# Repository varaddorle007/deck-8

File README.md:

# Deck-8

**An open-source 8-key macro pad with two knobs, a tiny screen and Bluetooth.** Everything is in this repo: the circuit board, the 3D-printable case, the firmware, and every file you need to order the parts.

*Click the preview for the full 30 second video with sound.*

> **Status: Rev A, designed and checked, but not yet built.** The board passes every automatic check (design rules, schematic checks, a fit check of the board in the case). The firmware compiles. But **no one has built one yet**, and the firmware has never run on real hardware. If you build one, you are the first. Please open an issue and tell us what happened, good or bad. See [Known risks](#known-risks).

## What it does

| | |
|---|---|
| **Keys** | 8 mechanical keys (MX-style, hot-swap, so you can change switches without soldering) in 2 rows of 4 |
| **Knobs** | 2 rotary knobs with push buttons (volume, scrolling, anything you map) |
| **Screen** | 0.96 inch OLED showing battery, connection and active layer |
| **Side buttons** | L1 and L2 on the left, System on the right, plus a power slide switch |
| **Lights** | RGB under every key, plus a glowing ring around the base |
| **Connections** | USB-C and Bluetooth (5 profiles) |
| **Battery** | Built-in 1000 mAh LiPo, charges over USB-C |
| **Brain** | Nordic nRF52840 (Raytac MDBT50Q module), running [ZMK](https://zmk.dev) firmware |
| **Remapping** | Change keys live in [ZMK Studio](https://zmk.studio), no rebuild needed |
| **Size** | Case 98 × 84 mm, 18 mm tall at the front rising to 30 mm at the back (the top tilts 8°). Board 92.8 × 76 mm, 4 layers |

### The layers

By default the 8 keys send **F13–F20**. No normal keyboard has those keys, so they never clash with anything. Bind them to anything you like in OBS, in your operating system, or in a Stream Deck-style app.

```
         [knob A]   [  OLED  ]   [knob B]
  [L1]   [ 1 ] [ 2 ] [ 3 ] [ 4 ]
  [L2]   [ 5 ] [ 6 ] [ 7 ] [ 8 ]            [SYS]
```

| Layer | How you get it | Keys 1–4 | Keys 5–8 | Knob A turn / press | Knob B turn / press |
|---|---|---|---|---|---|
| Bank 1 | default | F13 F14 F15 F16 | F17 F18 F19 F20 | volume / mute | ← → / play-pause |
| Media | hold L1 | prev, play/pause, next, mute | undo, redo, copy, paste | same | same |
| Bank 3 | hold L2 | Ctrl+F13–F16 | Ctrl+F17–F20 | same | same |
| System | hold SYS | Bluetooth profile 1–4 | clear profile, USB/Bluetooth, lights on/off, next effect | brightness / saturation | colour / unlock Studio |

On the System layer, L1 jumps to the bootloader (for updates) and L2 resets. Edit [`firmware/config/deck8.keymap`](firmware/config/deck8.keymap) to change any of this.

## Pictures

### The case

| | |
|---|---|
|  |  |
|  |  |
|  |  |

*Bottom right: the tray, with the battery on the left and the glowing ring's wall around the edge. The 3D renders show the board and its parts as simple boxes where a part has no 3D model.*

### How it stacks together

The board is a two-sided sandwich:

- **Underneath** are all the small electronic parts: the main chip, the charger, the USB-C port, the key lights and the 8 key sockets. The factory solders these on.
- **On top** are only the parts you touch: the 2 knobs and the screen.
- **The key switches are not soldered.** They push down from the top through a thin plate and click into the sockets underneath. A broken key is pulled out and replaced.

### The circuit board

| Top | Bottom |
|---|---|
|  |  |

| 3D view, top | 3D view, bottom |
|---|---|
|  |  |

The PCB 3D views show the bare board; most parts have no 3D model in KiCad's library.

Four layers: top (signals), a full ground plane, a split power plane (3.3 V and the LED supply), and the bottom (parts and signals). 1037 tracks, 585 vias, USB data lines 14.5 and 15.2 mm long with no vias.

| Ground layer | Power layer |
|---|---|
|  |  |

### The schematic

Seven sheets, all generated from [`hardware/tools/gen_schematic.py`](hardware/tools/gen_schematic.py). The full set is in [`docs/deck8-schematic.pdf`](docs/deck8-schematic.pdf).

| Power: USB-C, charger, regulator, LED switch | MCU: nRF52840 and crystal |
|---|---|
|  |  |

| Inputs: keys, buttons, knobs | Lighting | Display |
|---|---|---|
|  |  |  |

## Build one

This is the plain version. [`release/BUILD-GUIDE.md`](release/BUILD-GUIDE.md) has the same steps in more detail, and [`release/BUY-LIST.csv`](release/BUY-LIST.csv) lists every part.

### What it costs

An honest estimate, from October 2026 prices. **Check every number at the time you order:**

| Item | Rough cost |
|---|---|
| Assembled boards from JLCPCB (3–5 boards, with all the small parts, setup fees and shipping) | about $150–200 total (₹13,000–17,000) |
| Parts you buy yourself: screen, 2 encoders, battery, LED strip, 8 switches, keycaps, screws | about $20–35 per unit |
| Printing the case | about $10–35, depending on where you print |

The big cost is not the board itself. A bare board is cheap (5 boards for about $8 with leaded HASL finish). The cost is assembly: setup fees, "extended part" fees, the parts, and shipping. If you can solder, you can order bare boards and build them, but the main chip's pads are underneath it (see the next section), so you will need a hot-air station.

### Step 1: order the board

The ready-to-upload files are in [`release/deck8-RevA-manufacturing/1-PCB-order-JLCPCB/`](release/deck8-RevA-manufacturing/1-PCB-order-JLCPCB/):

| File | Upload it as |
|---|---|
| `deck8-RevA-gerbers.zip` | The board design |
| `deck8-RevA-bom-jlc.csv` | The parts list |
| `deck8-RevA-cpl-jlc.csv` | Where each part goes |

Settings (all listed in `JLC-ORDER-SETTINGS.md` in the same folder): 4 layers, 1.6 mm thick, ENIG finish (HASL also works but is less flat), tented vias, assembly on the **bottom side only**, and "Confirm parts placement" turned on.

**Watch for these on the JLCPCB parts page:**

- **The nRF52840 module (U5, MDBT50Q-1MV2) was out of stock** on 24 Oct 2026. Pick "Global Sourcing" for it, or buy it from Mouser or DigiKey and send it to JLC. Don't remove it from the order: its pads are under the module, so it can't be soldered by hand without hot air.
- **Four parts were swapped** to alternatives JLC had in stock. Each has the same footprint, checked against its datasheet: the 8 key sockets (HanElectricity CPG151101S11-16), the charger (BQ24074RGTT), the reset button (PTS810SJK) and the ring connector (Joint Tech A1001WR-S-03P).
- **Check the placement preview.** JLC doesn't know some of these parts' rotation. Check D1–D8, K1–K8, J4, SW1–SW5 and U5 sit correctly on their pads, and rotate any that don't.

### Step 2: buy the rest

[`release/BUY-LIST.csv`](release/BUY-LIST.csv) is the full list. Briefly:

- 2 × Bourns PEC11R-4220F-S0024 rotary encoders (through-hole)
- 4 × Würth 9774030243 M2 standoffs (SMD, not at LCSC)
- 0.96 inch SSD1306 I²C OLED module with its 4-pin header (pin order GND-VCC-SCL-SDA)
- 8 × MX-style switches and 8 × keycaps
- 1000 mAh LiPo with protection board and a JST-PH plug (**check the polarity**, see below)
- SK6812 LED strip (5 mm wide, 60 LEDs/m, 293 mm = 17 LEDs) and a 3-pin JST SH lead
- M2 hardware: 4 heat-set inserts (3 mm long), 4 × M2×5 **wafer-head** screws, 2 × M2×6 and 2 × M2×12 pan-head screws
- 4 rubber feet (8 mm), and a 1 mm acrylic lens (laser-cut from the DXF)
- To flash the bootloader once: a Tag-Connect TC2030-IDC-NL cable and an SWD probe

### Step 3: print the case

Files are in [`release/deck8-RevA-manufacturing/3-Enclosure/`](release/deck8-RevA-manufacturing/3-Enclosure/). All STLs are in millimetres, laid flat.

| Part | Qty | Material |
|---|---|---|
| Top shell | 1 | MJF or SLS nylon (best), or FDM PETG/ASA. Nylon takes heat-set inserts. |
| Bottom tray | 1 | MJF nylon or FDM PETG |
| Light ring | 1 | Clear or translucent (clear SLA resin, sanded frosted). It must let light through. |
| Knob | 2 | MJF nylon or SLA (one file, print two) |
| Buttons (L1, L2, System) | 1 each | MJF nylon or SLA |
| Switch plate | 1 | Laser-cut 1.5 mm steel, aluminium or FR-4 from the DXF (best), or printed |
| OLED lens | 1 | 1 mm clear or smoked acrylic, laser-cut from the DXF |

### Step 4: assemble

1. **Solder by hand:** the 4 standoffs on the bottom (ST1–ST4) and the 2 encoders on the top.
2. **Check power.** Plug in USB-C through a USB power meter: it should draw well under 100 mA. With the power switch on, TP2 (VSYS) should read about 4.4 V and TP4 (+3V3) 3.3 V, measured against TP6 (GND).
3. **Flash the bootloader once** (next section).
4. **Melt the 4 heat-set inserts** into the shell bosses.
5. **Fit the OLED.** Shell upside down: drop in the lens, then the screen module glass-down with its header pins pointing up. Clip the header's short pins to 1 mm.
6. **Fit the board.** Lower it onto the bosses with the OLED pins through J5. Screw it down with the four wafer-head screws, then solder the 4 J5 pins from underneath. The shell sets the screen height, so do this *after* screwing the board in.
7. **Switches.** Put the plate in, then push the 8 switches through it into the sockets.
8. **Battery.** **Check the polarity first**: the red wire must land on J2 pin 1 (VBAT). Swap the crimps in the plug if not. Then plug in the cell; it sits in the tray's fence.
9. **Ring.** Stick the LED strip round the light wall, LEDs facing out. Solder the SH lead (VLED, DIN, GND) and plug it into J4.
10. **Close up.** Fit the ring, then close the tray with the M2×6 screws (front) and M2×12 (back). Stick on the feet.
11. **Finish.** Knobs on the shafts, buttons, and keycaps.

### Step 5: firmware

The firmware is ready-built: [`release/deck8-RevA-manufacturing/4-Firmware/deck8.uf2`](release/deck8-RevA-manufacturing/4-Firmware/deck8.uf2).

**Once per board** (a new nRF52840 is empty): put the bootloader on through the Tag-Connect pads J3.

1. Download `nice_nano_bootloader-0.11.0_s140_6.1.1.hex` from the [Adafruit bootloader releases](https://github.com/adafruit/Adafruit_nRF52_Bootloader/releases/tag/0.11.0). Its flash layout matches this board.
2. Connect the Tag-Connect cable and an SWD probe, power the board over USB, then run:

```bash
nrfjprog --program nice_nano_bootloader-0.11.0_s140_6.1.1.hex --chiperase --verify --reset
```

3. A USB drive called **NICENANO** appears. Copy `deck8.uf2` onto it. The board restarts as "Deck-8".

**Updates:** hold SYS and press L1, or double-press the RESET button (SW2), and copy the new `.uf2` onto the drive.

**First-power-up checks** (the firmware has never run on real hardware, so check these):

- **Screen upside down?** Add `segment-remap;` and `com-invdir;` to the `oled` node in `firmware/boards/deck8/deck8_nrf52840_zmk.dts`. **Blank?** Delete `inversion-on;`.
- **A knob turns the wrong way?** Swap its two values in `sensor-bindings` in the keymap. **Two steps per click?** Set `steps = <48>` for that encoder.
- **Ring colours wrong, or the wrong length?** Change `color-mapping` or `chain-length` in the `ring_leds` node, and `chain-length` in `all_leds` (8 key LEDs + ring LEDs).

See [`firmware/README.md`](firmware/README.md) for how the firmware is built and what each file does.

## What's in this repo

```
deck-8/
├── hardware/             the circuit board (KiCad 10)
│   ├── main/             the KiCad project: open deck8.kicad_pro
│   ├── lib/              the 4 custom footprints
│   ├── exports/          the board as a 3D STEP file (deck8_pcb.step)
│   ├── tools/            Python that generates, routes and checks the board and writes the fab files
│   └── README.md         how the board was designed, routed and checked
├── mechanical/           the case (Autodesk Fusion)
│   ├── fusion/Deck8Model/  script that builds the whole case; change a number and re-run
│   └── exports/          STEP, STL, renders and the clash-check report
├── firmware/             ZMK firmware: keymap, board definition, LED and battery code
├── release/              everything ready to upload, print and flash, plus the build guide and buy list
├── media/                the 30 second promo video
└── docs/                 images and the schematic PDF
```

Nothing is drawn by hand. The schematic, the board layout and the case are all produced by scripts, so a change is a few lines of code and a re-run. That also means **edit the scripts, not the generated files**.

## Rebuild it from source

You need macOS or edit the paths: the scripts point to KiCad at `/Applications/KiCad/KiCad.app`. You'll want KiCad 10, Python 3, Autodesk Fusion (the free personal or education licence works), and a C compiler for the router.

**Board**, from `hardware/tools`. `KPY` is KiCad's own Python, which includes `pcbnew`:

```bash
KPY=/Applications/KiCad/KiCad.app/Contents/Frameworks/Python.framework/Versions/Current/bin/python3
python3 gen_schematic.py && python3 check_schematic.py
$KPY gen_pcb.py && $KPY route_pcb.py && python3 check_pcb.py
$KPY make_fab.py
```

About a minute in total, with the same result every time. `check_pcb.py` runs KiCad's design-rule check and fails on anything. `make_fab.py` refuses to run unless the check passes, then writes the Gerbers, BOM and pick-and-place files and reads them all back to verify them.

The router is a small A\* autorouter written for this project (`hardware/tools/route_pcb.py` plus a C core in `hardware/tools/router/maze.c`, compiled on first run).

**Case**, in Fusion: open Utilities → Add-Ins → Scripts and Add-Ins, add the folder `mechanical/fusion/Deck8Model`, and run it. It builds the case, loads the PCB from `hardware/build/deck8_pcb.step`, and writes the report and exports. If you copy the script into Fusion's own scripts folder instead, put the path of this repo in a file called `deck8_root.txt` next to it, or set the `DECK8_ROOT` environment variable. A clean build reports 0 errors and 0 clashes.

**Firmware**, from `firmware/`:

```bash
tools/setup_toolchain.sh   # once: about 4 GB into ~/zmk-build, nothing system-wide
tools/build.sh             # builds out/deck8.uf2
```

**Release files**: `python3 release/tools/make_release.py` collects the latest board, case and firmware files into `release/deck8-RevA-manufacturing/`.

## Known risks

Rev A is a first prototype. In order of how likely they are to bite:

1. **Nothing has been powered up.** The design passes every check a computer can run, but first prototypes nearly always have a surprise.
2. **The firmware has never run on a real board.** The screen orientation, knob direction and ring length are the likely first fixes (each is one line).
3. **Part stock.** The nRF52840 module was out of stock at JLC. Stock changes daily; check before you order.
4. **Footprints are checked against datasheets, not against real parts.** The key sockets are HanElectricity parts sold under Kailh's number; the land pattern matches their drawing, but nobody has plugged a switch in.
5. **The LED-ring plug length is assumed** (3.0 mm). JST doesn't draw the mated length for that connector.
6. **The cells' polarity isn't standard.** JST-PH leads from different sellers are wired both ways. Check before plugging in.
7. **The lights need a charged battery.** The SK6812 LEDs need about 3.7 V, so on battery below that the firmware switches the colours off.
8. **Power saving is off.** The chip runs on its LDO. Raytac's material doesn't confirm the DC/DC inductor is fitted, and turning DC/DC on without it stops the chip. Once you have a board, try it (see `firmware/boards/deck8/deck8_nrf52840_zmk_defconfig`).

## Help wanted

- **Build one and report back.** Photos, measurements, what broke.
- **A cheaper variant.** The full board costs a lot to have assembled. A 2-layer, hand-solderable board that takes a ready-made nRF52840 board (nice!nano style) would cost far less. If you design one, send it.
- **Other fabs.** The BOM uses LCSC part numbers for JLCPCB. Ports to PCBWay, or to Indian assembly houses, are welcome.
- **Windows and Linux.** The scripts assume macOS paths.
- **Case ideas.** Different materials, a flat version, a travel lid.

Open an issue or a pull request.

## License

[MIT](LICENSE) for the hardware design files, the case, the code and the docs. Do what you like with them, including selling them; please keep the licence notice. Third-party material is listed in [NOTICE.md](NOTICE.md).

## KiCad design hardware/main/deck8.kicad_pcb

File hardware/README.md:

# Deck-8 hardware (KiCad 10)

`main/deck8.kicad_pro` is the project. Open it in KiCad 10. The files are written in the KiCad 9 format, which KiCad 10 opens and upgrades the first time you save.

## Regenerate and check

The schematic and the board, routing included, are generated, so edit the scripts in `tools/`, not the KiCad files. `KPY` is KiCad's own Python, which ships `pcbnew`:

```bash
KPY=/Applications/KiCad/KiCad.app/Contents/Frameworks/Python.framework/Versions/Current/bin/python3
```

```bash
cd tools && python3 gen_schematic.py && python3 check_schematic.py
```

```bash
cd tools && $KPY gen_pcb.py && $KPY route_pcb.py && python3 check_pcb.py
```

```bash
cd tools && $KPY make_fab.py
```

The whole chain takes about a minute and gives the same board every time. `route_pcb.py` discards all tracks, vias and its own zones, then routes again from the placement. It depends only on the placement, not on the order KiCad saves footprints in.

`trim_footprints.py` is a one-off: it copies the stock USB-C, slide-switch and MDBT50Q footprints into `lib/deck8.pretty` without the silk that runs past the board edge. Re-run it (before `gen_schematic.py`) only if one of those parts moves; `gen_pcb.py` warns when it has to trim edge silk itself.

## Fabrication package (JLCPCB)

`tools/make_fab.py` writes `build/fab/`. It refuses to run unless DRC with schematic parity reports nothing, and its `README.md` there lists the JLC order settings. The package:

- **`deck8-RevA-gerbers.zip`:** 11 Gerber layers, PTH and NPTH Excellon drill files and drill maps. They use JLC's KiCad settings: Protel extensions, no X2 or netlist attributes, mask subtracted from silk. Gerbers, drill and CPL share the drill/place origin at the board's lower-left corner.
- **`deck8-RevA-bom-jlc.csv` and `deck8-RevA-cpl-jlc.csv`:** 34 BOM lines, 78 bottom-side placements, every one with an LCSC part.
  - Bottom angles are mirrored the way JLC reads them, (180° − KiCad angle).
  - Package corrections come from the JLCKicadTools table that kicad-jlcpcb-tools uses: SOT-23 −90°, QFN +270°, HRO USB-C +180°, JST-PH +180°.
  - Placements sit on the centre of each part's soldered pads. The hot-swap sockets are listed as bottom parts, although their footprint sits on top.
- **`deck8-RevA-bom-full.csv`:** every fitted part with who fits it. JLC fits all bottom SMD parts. You fit by hand the two encoders, the OLED module at J5 (its own header, soldered once the board is in the shell) and the four Würth standoffs (not stocked at LCSC). R6/R7 are not fitted.
- **`deck8-RevA-assembly-top.pdf` and `-bottom.pdf`:** fab-layer drawings for the hand-fitted parts.
- **The order number:** JLC prints it where the bottom silk reads "JLCJLCJLCJLC", beside "Deck-8 Rev A". Pick "Specify a location".

`tools/gerber_check.py` (system Python with PIL) then reads all of it back without KiCad and compares it with facts measured on the board. On 23 Oct 2026 all 19 checks passed:
- the outline;
- hole counts per diameter in both drill files;
- one flash per via and per pad on each copper layer;
- no mask opening on any via;
- paste only on the bottom;
- BOM, CPL and board listing the same parts, each with an LCSC number, every placement on the board beside its own pads.

It also renders the Gerbers to `check_*.png` for a visual check.

The LCSC numbers are an `LCSC` field on each schematic symbol. Passives come from one table in `gen_schematic.py`, so the BOM can't drift from the schematic. Every number was checked on lcsc.com / jlcpcb.com on 23 Oct 2026; stock and prices change, so recheck them at order time.

## PCB (Rev A, routed)

- **Board:** 4 layers, 1.6 mm, 92 × 76 mm with 9 mm back and 3 mm front chamfers. A 0.8 mm tab on the left edge carries the power slider so its lever reaches the wall slot.
- **Stack-up:**
  - F.Cu: signals plus a GND pour.
  - In1: solid GND.
  - In2: +3V3 behind Y +20.3 and VLED in front of Y +19.7 (the keys and LED drivers).
  - B.Cu: parts, signals and a GND pour.
- **Tracks:**
  - 0.2 mm for signals.
  - 0.4 mm for +3V3 and the LDO output.
  - 0.5 mm for VBUS.
  - 0.8 mm for VBUS_IN, VSYS, VBAT and VLED_SW. These neck down only where a pad is narrower: 0.2 mm at the charger's 0.5 mm-pitch pins, 0.45 mm at the USB-C VBUS pins.
  - Pins that only sense a rail get a thin branch: the charger's EN1, the module's VBUS detect, the ESD part's VBUS pin, the power switch and the test points.
- **Vias:** 0.6 / 0.3 mm throughout (JLC standard). Every SMD pad on GND, +3V3 or VLED has its own via into its plane. The charger's GND pins join its exposed pad, which has its own thermal vias. 317 GND stitching vias on a 4 mm grid tie the outer pours to In1, so no pour piece is left floating.
- **USB:** D+ 14.5 mm and D− 15.2 mm, no vias, through the USBLC6 that sits in line between the connector and the module.
- **Crystal:** XL1/XL2 are 6.4 / 8.0 mm, no vias, routed before any other signal.
- **Keep-outs (enforced by DRC):**
  - Antenna: nothing on any layer.
  - Shell bosses and screw heads: no tracks or vias within 2.5 mm of H1–H4 on either side.
  - Tag-Connect: no vias under its pads.
  - Light wall: no bottom parts in front of Y −24.2.
- **Silkscreen:** every reference sits in the first free spot around its part at 0.8 mm. Six on the crowded bottom (C2, C11, C25, R6, R12, R14) have no free spot, so they are only on the fab layer.
- **DRC (23 Oct 2026):** 0 errors, 0 warnings, 0 unrouted, schematic parity clean. 1037 tracks, 585 vias (317 of them stitching).
- `main/deck8.kicad_dru` adds four rules:
  - relaxed clearances inside three stock land patterns (SKRT side buttons, Würth standoff rings, SK6812MINI-E cut-outs);
  - one thermal spoke is enough on the outer GND pours, since every GND pad already reaches In1.
- **Outputs in `build/`:**
  - `drc.json`, `route_report.json`, `pcb_placement_report.json`.
  - `pcb_top/bottom/iso_*.png` and `pcb_views.png` (3D views); `pcb_layers.png` (each copper layer).
  - `deck8_pcb.step` for the Fusion fit check.
- **3D models:** this KiCad install has no 3D models for the MX switch or EC11 encoder, so the renders and STEP show only their pads.

### How the router works

`tools/route_pcb.py` drives a small A* router in C (`tools/router/maze.c`, compiled on the first run). The board is sampled on a 0.1 mm grid, offset half a cell so the 0.05 mm pad rows land on cell centres.

- **Clearance:** for every layer, each cell stores the clearance-adjusted distance to the nearest copper of another net. A track may pass only where that distance covers its half-width, plus the most a step can stray from a checked cell centre. Pad and hole clearances, the 0.3 mm edge clearance, hole-to-hole spacing and the keep-outs are the board's own rules, so every route is legal by construction. KiCad's DRC then confirms it.
- **Shape:** the search tracks heading, so turns cost something and corners sharper than 90° are not allowed. Routes come out as straight runs with 45° bends.
- **Order:**
  1. power and USB;
  2. the plane vias;
  3. the crystal;
  4. the remaining signals, shortest first.
- **Rip-up:** when a pin can't be reached, the router finds the path that crosses the fewest other tracks and rips up only those nets. It then routes the stuck pin and re-routes the ripped nets around it. USB and the crystal are never ripped.
- **Escapes:** three charger pins on a 0.5 mm-pitch corner get a via before anything else is routed, each on its own side (EN1 south-east, PGOOD south, CHG west), so they don't box each other in.

### Choices made while laying out

- **Encoders:** mirrored, so both pin rows face the walls.
- **Tag-Connect:** at (−9, 25.5) under the OLED. Its alignment pins can't go under a switch.
- **J4:** takes its plug from the left, because a front entry would hit the light wall.
- **Plug space:** no bottom part stands where J2's or J4's mated plug goes. The boxes come from JST's drawings (`PLUG` in `gen_pcb.py`), and the Fusion check uses them too. That is why the battery-sense parts sit past the end of J2's plug, under the wires, not where the plug goes.
- **Hand-placed parts:** the parts that serve one pin are placed by hand, not by the scan:
  - the USB ESD part, in line between USB-C and the module's D+/D−, with the CC resistors either side of the pair;
  - the module's VBUS and VDD caps, right under their pins;
  - the crystal and its load caps, as close to their pins as the H2 screw head allows.
- **Charger section:** turned so IN faces the fuse, OUT faces the LDO and the LED switch, and BAT faces the battery connector. Its setup resistors sit in a row above the charger; the LDO, its caps and the status pull-ups in a row below.
- **LED drivers:** the LED switch sits with its input cap between ST1 and J4's plug. Right of J4, each data buffer is grouped with its resistor and cap.
- **Key LED chain:** keys 5-6-7-8-4-3-2-1. Data runs left to right along the front row, up the right side, and back along the back row, whose LEDs are turned 180° so each DOUT faces the next DIN. No data line crosses the board.

## Sheets

| Sheet | Contents |
|---|---|
| Overview | Sheet index, GPIO plan (generated from the pin map), review list |
| Power | USB-C (CC1/CC2 own 5.1 k), PTC, USBLC6, BQ24074 (USB500, 494 mA), battery + divider, TPS7A0533 3.3 V (EN = power switch), TPS22917 LED switch, 0 Ω measurement links, test points |
| MCU | MDBT50Q-1MV2 (normal voltage mode), decoupling, 32.768 kHz crystal, Tag-Connect SWD, reset |
| Inputs | K1–K8, L1/L2/System side buttons, two EC11 encoders with push |
| Lighting | Two SN74LV1T125 shifters on VLED, D1–D8 SK6812MINI-E chain (keys 5-6-7-8-4-3-2-1), ring strip connector + 100 µF |
| Display | OLED header (GND-VCC-SCL-SDA), I²C pull-ups, decoupling |
| Mechanical | H1–H4 shell holes, ST1–ST4 M2×3 SMD standoffs, fiducials |

## GPIO plan (nRF52840)

Each signal leaves the module on the edge that faces where it goes:
- **East:** keys 3, 4 and 8, the right knob and the System button.
- **South:** keys 2, 5, 6 and 7, and the LED lines.
- **West:** key 1, the left knob, L1/L2, I²C and charger status.

The map comes from a minimum-total-length matching of free pads to destinations on this placement, which also keeps the escapes from crossing. Constraints:
- **West edge:** west-going signals use the module's inner and centre pads, which drop a via straight to the free top layer. The outer west pads could only leave into the gap beside the USB ESD part.
- **South edge:** the outer south pads P0.04, P0.06, P0.08 and P1.09 stay free, because the crystal lines run under them.
- **Pin types:** I²C and LED data are on P0 full-speed pins, and BAT_SENSE is on an analog input.

| Function | Pins |
|---|---|
| Keys 1–8 | P0.14, P1.08, P0.28, P0.31, P0.12, P0.07, P0.27, P0.30 |
| L1, L2, System | P1.01, P0.21, P0.29 |
| Knob A (A/B/push) | P1.02, P0.25, P1.00 |
| Knob B (A/B/push) | P1.15, P1.11, P1.13 |
| I²C SDA / SCL | P0.16 / P0.19 |
| LED data: ring / keys | P0.11 / P0.05 (SPI MOSI; the SPI clock goes to a spare unconnected pin) |
| LED_EN, BAT_SENSE (AIN0), CHG_N, PGOOD_N | P0.26, P0.02, P0.23, P1.03 |
| Reset, LFXO | P0.18, P0.00/P0.01 |

All other GPIO are marked no-connect. P0.09/P0.10 (NFC) are left unused. The key LED chain index i drives key 5, 6, 7, 8, 4, 3, 2, 1 in that order.

## Placement from the Fusion model

`gen_schematic.py` reads the layout constants straight out of `../mechanical/fusion/Deck8Model/Deck8Model.py`, so keys, knobs, holes, side switches, USB-C and the board outline can't drift from the enclosure. Every positioned part has a `Deck8_Place` field, and `placement.json` lists all 40 of them. Coordinates are in the PCB plane: origin at the key-grid centre on the PCB top, +Y toward the back.

## Changes from the plan

- 3.3 V regulator: **TPS7A0533** (1 µA Iq) instead of TPS7A02. KiCad's stock library has no TPS7A02; this part draws the same tiny standby current.
- LED switch: **TPS22917** instead of TPS22918. It has the same CT (slew) and QOD (discharge) pins and is in the stock library. QOD goes to VOUT through R20 (0 Ω) so ERC stays clean.
- OLED module: its header row faces the keys (Y ≈ 23 mm). With the header at the back, the pins would land outside the 76 mm board.
- OLED mounting: no socket. A socket plus the module's own header puts the glass 11 mm off the board, and the shell leaves 7 mm. The module's header pins go through J5, now a `PinHeader_1x04` footprint with no 3D model, and are soldered once the board is in the shell (`../mechanical/README.md`). The copper is the same as the socket footprint's.
- GPIO map and key LED chain order changed during layout (above). Firmware isn't written yet, so nothing else depends on them.
- Level shifters: **SN74LV1T125** instead of 74AHCT1G125. AHCT needs a 4.5–5.5 V supply, and VLED is 3.0–4.4 V. The LV1T125 has TTL-level inputs on any supply from 1.6 to 5.5 V and the same pinout and footprint.
- Crystal: Seiko SC-32S, 32.768 kHz, 20 ppm, **9 pF** load (C97605). The two 12 pF caps in series give 6 pF, plus about 3 pF from the pins and traces.

## Checked against the TI BQ24074 datasheet

- ITERM and TMR left open give the default 10 % termination current and the default safety timers, so R6 and R7 stay unfitted. Tying TMR to GND would disable the timers.
- TS: a 10 kΩ fixed resistor to VSS when the cell has no thermistor (R3).
- EN1 high and EN2 low select 450–500 mA input (USB500). The EN pins have internal pull-downs, but the datasheet says not to leave them open.
- K_ISET = 890 AΩ, so the 1.8 kΩ R4 sets 494 mA. OUT (VSYS) regulates at 4.4 V.

## Review before ordering

1. K1–K8 use `Deck8:SW_MX_Hotswap_Kailh_1u_NorthLED` (`lib/deck8.pretty`, registered in `main/fp-lib-table`). Pad and hole positions come from the MX pin pattern; check them against the Kailh CPG151101S11 drawing.
2. Battery J2 polarity must match the cell; JST-PH polarity is not standard.
3. OLED J5: confirm the pin order and header position against the module you buy. Its header needs the usual 6 mm long side, since the pins go through the board.
4. Stock at JLC on 24 Oct: the MDBT50Q-1MV2 (U5, C5118826) had none. Pick JLC Global Sourcing for it when you order, or buy it at Mouser/DigiKey and consign it. Four other lines were short and now use same-footprint parts that JLC has in stock: K1–K8 HanElectricity CPG151101S11-16 (C41430893), U2 BQ24074RGTT (C2861252), SW2 PTS810SJK (C221896), J4 Joint Tech A1001WR-S-03P (C371509). Their drawings match the land patterns.
5. In JLC's placement preview, check the parts whose package has no rotation entry before confirming: the sockets, LEDs, module, JST-SH connector and the switches. The list is in `build/fab/README.md`.
6. SK6812MINI-E needs VDD ≥ 3.7 V, so firmware must turn the RGB off below about 3.7 V on battery.
7. Done 23 Oct: the Fusion fit check of `build/deck8_pcb.step` in the enclosure shows 0 interferences (`../mechanical/README.md`).

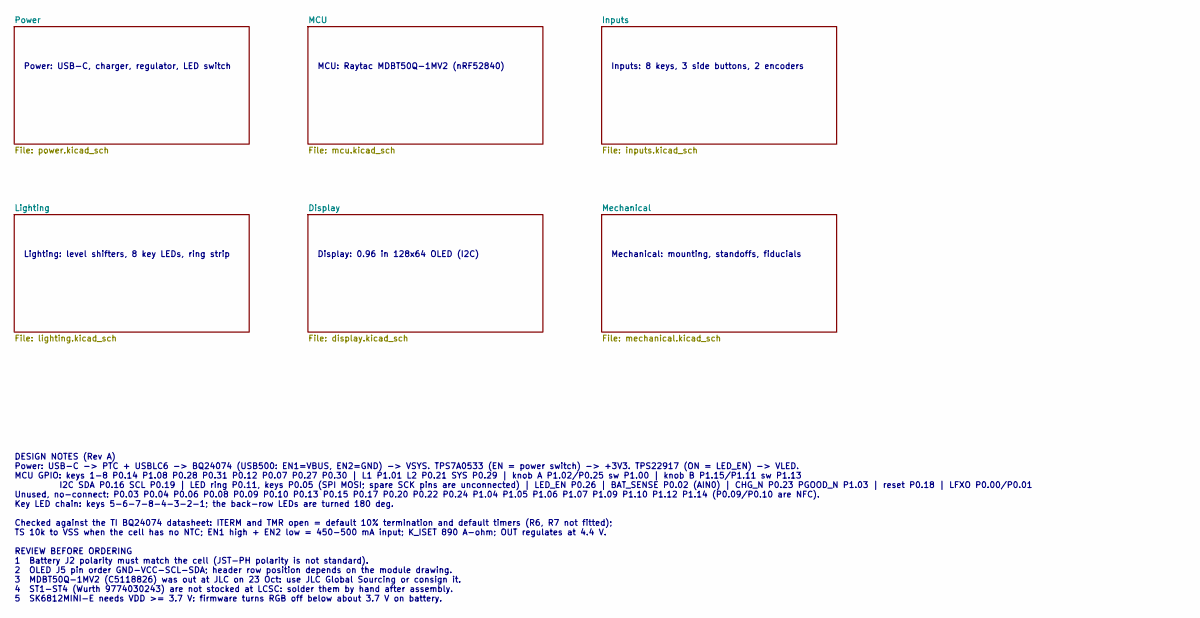
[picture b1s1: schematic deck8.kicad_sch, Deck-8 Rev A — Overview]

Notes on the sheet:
Power: USB-C, charger, regulator, LED switch
MCU: Raytac MDBT50Q-1MV2 (nRF52840)
Inputs: 8 keys, 3 side buttons, 2 encoders
Lighting: level shifters, 8 key LEDs, ring strip
Display: 0.96 in 128x64 OLED (I2C)
Mechanical: mounting, standoffs, fiducials
DESIGN NOTES (Rev A) Power: USB-C -> PTC + USBLC6 -> BQ24074 (USB500: EN1=VBUS, EN2=GND) -> VSYS. TPS7A0533 (EN = power switch) -> +3V3. TPS22917 (ON = LED_EN) -> VLED. MCU GPIO: keys 1-8 P0.14 P1.08 P0.28 P0.31 P0.12 P0.07 P0.27 P0.30 | L1 P1.01 L2 P0.21 SYS P0.29 | knob A P1.02/P0.25 sw P1.00 | k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

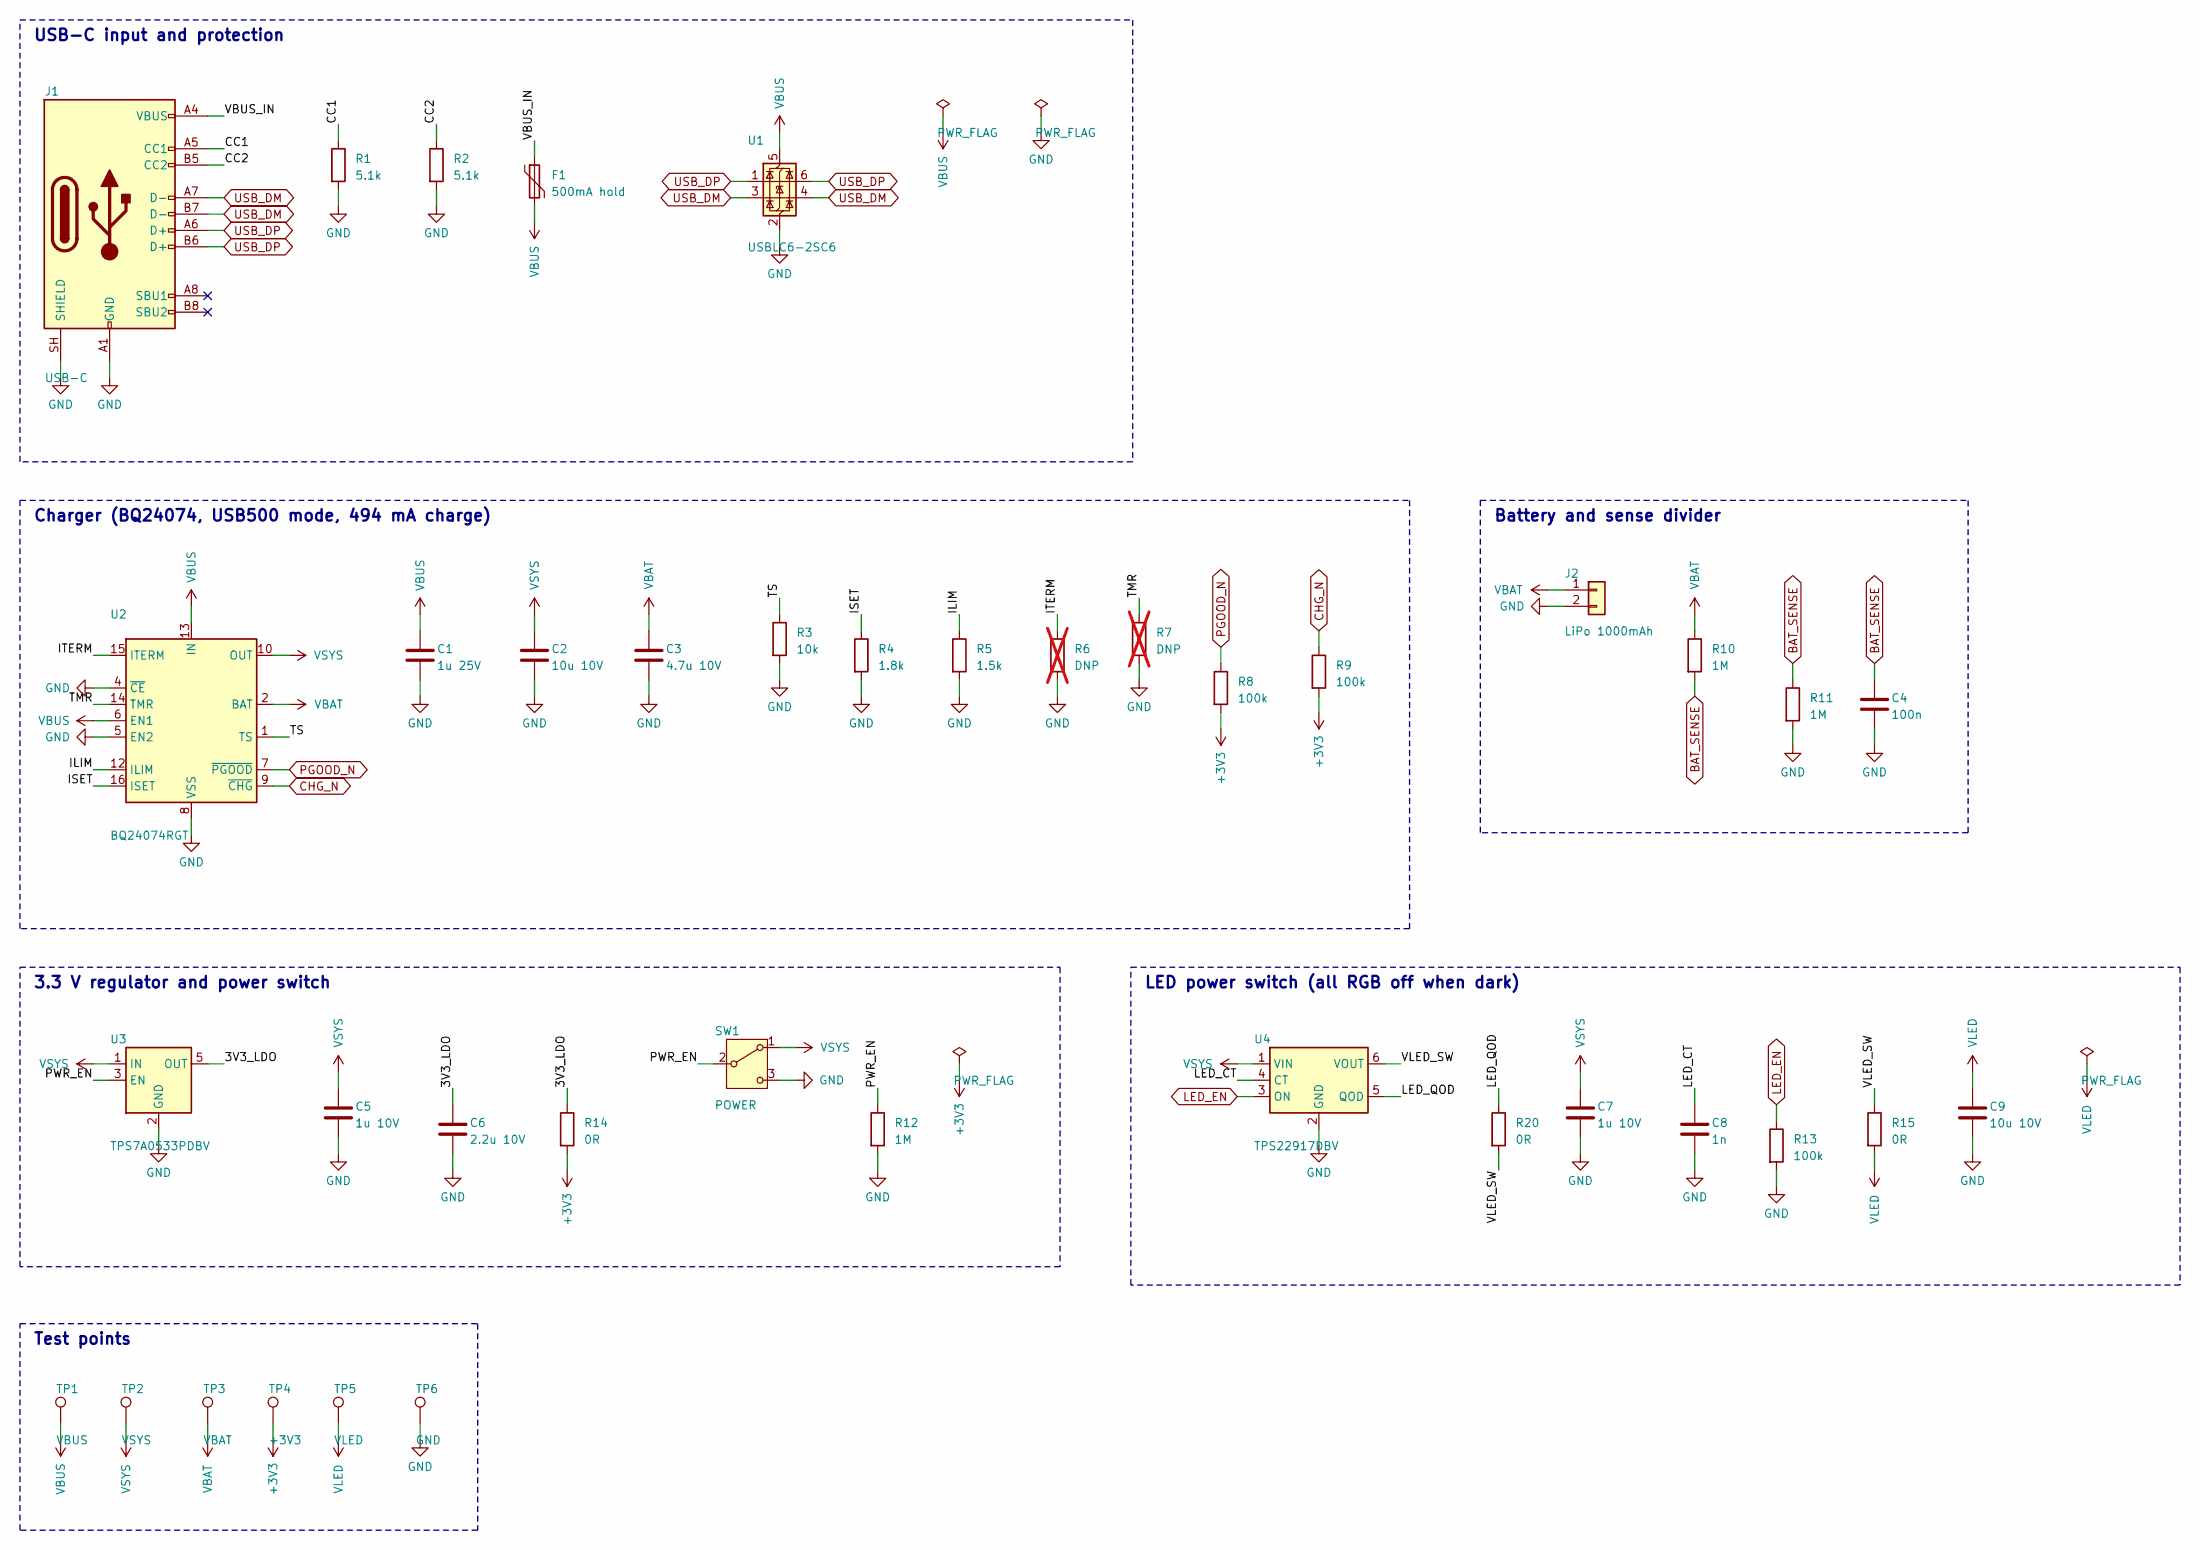
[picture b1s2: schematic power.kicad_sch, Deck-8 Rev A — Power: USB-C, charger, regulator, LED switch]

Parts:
C1: 1u 25V; C_0603_1608Metric; MPN CL10A105KB8NNNC (50 V X5R); LCSC C15849
C2, C9: 10u 10V; C_0603_1608Metric; MPN CL10A106KP8NNNC (10 V X5R); LCSC C19702
C3: 4.7u 10V; C_0603_1608Metric; MPN CL10A475KO8NNNC (16 V X5R); LCSC C19666
C4: 100n; C_0603_1608Metric; MPN CC0603KRX7R9BB104 (50 V X7R); LCSC C14663
C5, C7: 1u 10V; C_0603_1608Metric; MPN CL10A105KB8NNNC (50 V X5R); LCSC C15849
C6: 2.2u 10V; C_0603_1608Metric; MPN CL10A225KO8NNNC (16 V X5R); LCSC C23630
C8: 1n; C_0603_1608Metric; MPN CL10B102KB8NNNC (50 V X7R); LCSC C1588
F1: 500mA hold; Fuse_1206_3216Metric; MPN Littelfuse 1206L050YR (6 V); LCSC C163512
J1: USB-C; USB_C_Receptacle_HRO_TYPE-C-31-M-12; MPN HRO TYPE-C-31-M-12; LCSC C165948
J2: LiPo 1000mAh; JST_PH_S2B-PH-SM4-TB_1x02-1MP_P2.00mm_Horizontal; MPN JST S2B-PH-SM4-TB(LF)(SN); LCSC C295747
R1, R2: 5.1k; R_0603_1608Metric; MPN UNI-ROYAL 0603WAF5101T5E; LCSC C23186
R3: 10k; R_0603_1608Metric; MPN UNI-ROYAL 0603WAF1002T5E; LCSC C25804
R4: 1.8k; R_0603_1608Metric; MPN UNI-ROYAL 0603WAF1801T5E; LCSC C4177
R5: 1.5k; R_0603_1608Metric; MPN UNI-ROYAL 0603WAF1501T5E; LCSC C22843
R6, R7: DNP; R_0603_1608Metric; not fitted
R8, R9, R13: 100k; R_0603_1608Metric; MPN UNI-ROYAL 0603WAF1003T5E; LCSC C25803
R10, R11, R12: 1M; R_0603_1608Metric; MPN UNI-ROYAL 0603WAF1004T5E; LCSC C22935
R14, R15, R20: 0R; R_0603_1608Metric; MPN UNI-ROYAL 0603WAF0000T5E; LCSC C21189
SW1: POWER; SW_SPDT_PCM12; MPN C&K PCM12SMTR; LCSC C221841
TP1: VBUS; TestPoint_Pad_D1.0mm
TP2: VSYS; TestPoint_Pad_D1.0mm
TP3: VBAT; TestPoint_Pad_D1.0mm
TP4: +3V3; TestPoint_Pad_D1.0mm
TP5: VLED; TestPoint_Pad_D1.0mm
TP6: GND; TestPoint_Pad_D1.0mm
U1: USBLC6-2SC6; SOT-23-6; MPN ST USBLC6-2SC6; LCSC C7519
U2: BQ24074RGT; VQFN-16-1EP_3x3mm_P0.5mm_EP1.6x1.6mm_ThermalVias; MPN TI BQ24074RGTT; LCSC C2861252
U3: TPS7A0533PDBV; SOT-23-5; MPN TI TPS7A0533PDBVR; LCSC C493453
U4: TPS22917DBV; SOT-23-6; MPN TI TPS22917DBVR; LCSC C2681320

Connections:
+3V3: R8.2, R9.2, R14.2, TP4.1; also elsewhere on the board
/Power/3V3_LDO: C6.1, R14.1, U3.5 (OUT)
/Power/CC1: J1.A5 (CC1), R1.1
/Power/CC2: J1.B5 (CC2), R2.1
/Power/ILIM: R5.1, U2.12 (ILIM)
/Power/ISET: R4.1, U2.16 (ISET)
/Power/ITERM: R6.1, U2.15 (ITERM)
/Power/LED_CT: C8.1, U4.4 (CT)
/Power/LED_QOD: R20.1, U4.5 (QOD)
/Power/PWR_EN: R12.1, SW1.2 (B), U3.3 (EN)
/Power/TMR: R7.1, U2.14 (TMR)
/Power/TS: R3.1, U2.1 (TS)
/Power/VBUS_IN: F1.1, J1.A4 (VBUS), J1.A9 (VBUS), J1.B4 (VBUS), J1.B9 (VBUS)
/Power/VLED_SW: R15.1, R20.2, U4.6 (VOUT)
BAT_SENSE: C4.1, R10.2, R11.1; also elsewhere on the board
CHG_N: R9.1, U2.9 (~CHG); also elsewhere on the board
GND: C1.2, C2.2, C3.2, C4.2, C5.2, C6.2, C7.2, C8.2, C9.2, J1.A1 (GND), J1.A12 (GND), J1.B1 (GND), J1.B12 (GND), J1.SH (SHIELD), J2.2, R1.2, R2.2, R3.2, R4.2, R5.2, R6.2, R7.2, R11.2, R12.2, R13.2, SW1.3 (C), TP6.1, U1.2 (GND), U2.4 (~CE), U2.5 (EN2), U2.8 (VSS), U2.17 (VSS), U3.2 (GND), U4.2 (GND); also elsewhere on the board
LED_EN: R13.1, U4.3 (ON); also elsewhere on the board
PGOOD_N: R8.1, U2.7 (~PGOOD); also elsewhere on the board
USB_DM: J1.A7 (D-), J1.B7 (D-), U1.3 (I/O2), U1.4 (I/O2); also elsewhere on the board
USB_DP: J1.A6 (D+), J1.B6 (D+), U1.1 (I/O1), U1.6 (I/O1); also elsewhere on the board
VBAT: C3.1, J2.1, R10.1, TP3.1, U2.2 (BAT), U2.3 (BAT)
VBUS: C1.1, F1.2, TP1.1, U1.5 (VBUS), U2.6 (EN1), U2.13 (IN); also elsewhere on the board
VLED: C9.1, R15.2, TP5.1; also elsewhere on the board
VSYS: C2.1, C5.1, C7.1, SW1.1 (A), TP2.1, U2.10 (OUT), U2.11 (OUT), U3.1 (IN), U4.1 (VIN)

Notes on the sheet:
USB-C input and protection
Charger (BQ24074, USB500 mode, 494 mA charge)
Battery and sense divider
3.3 V regulator and power switch
LED power switch (all RGB off when dark)
Test points

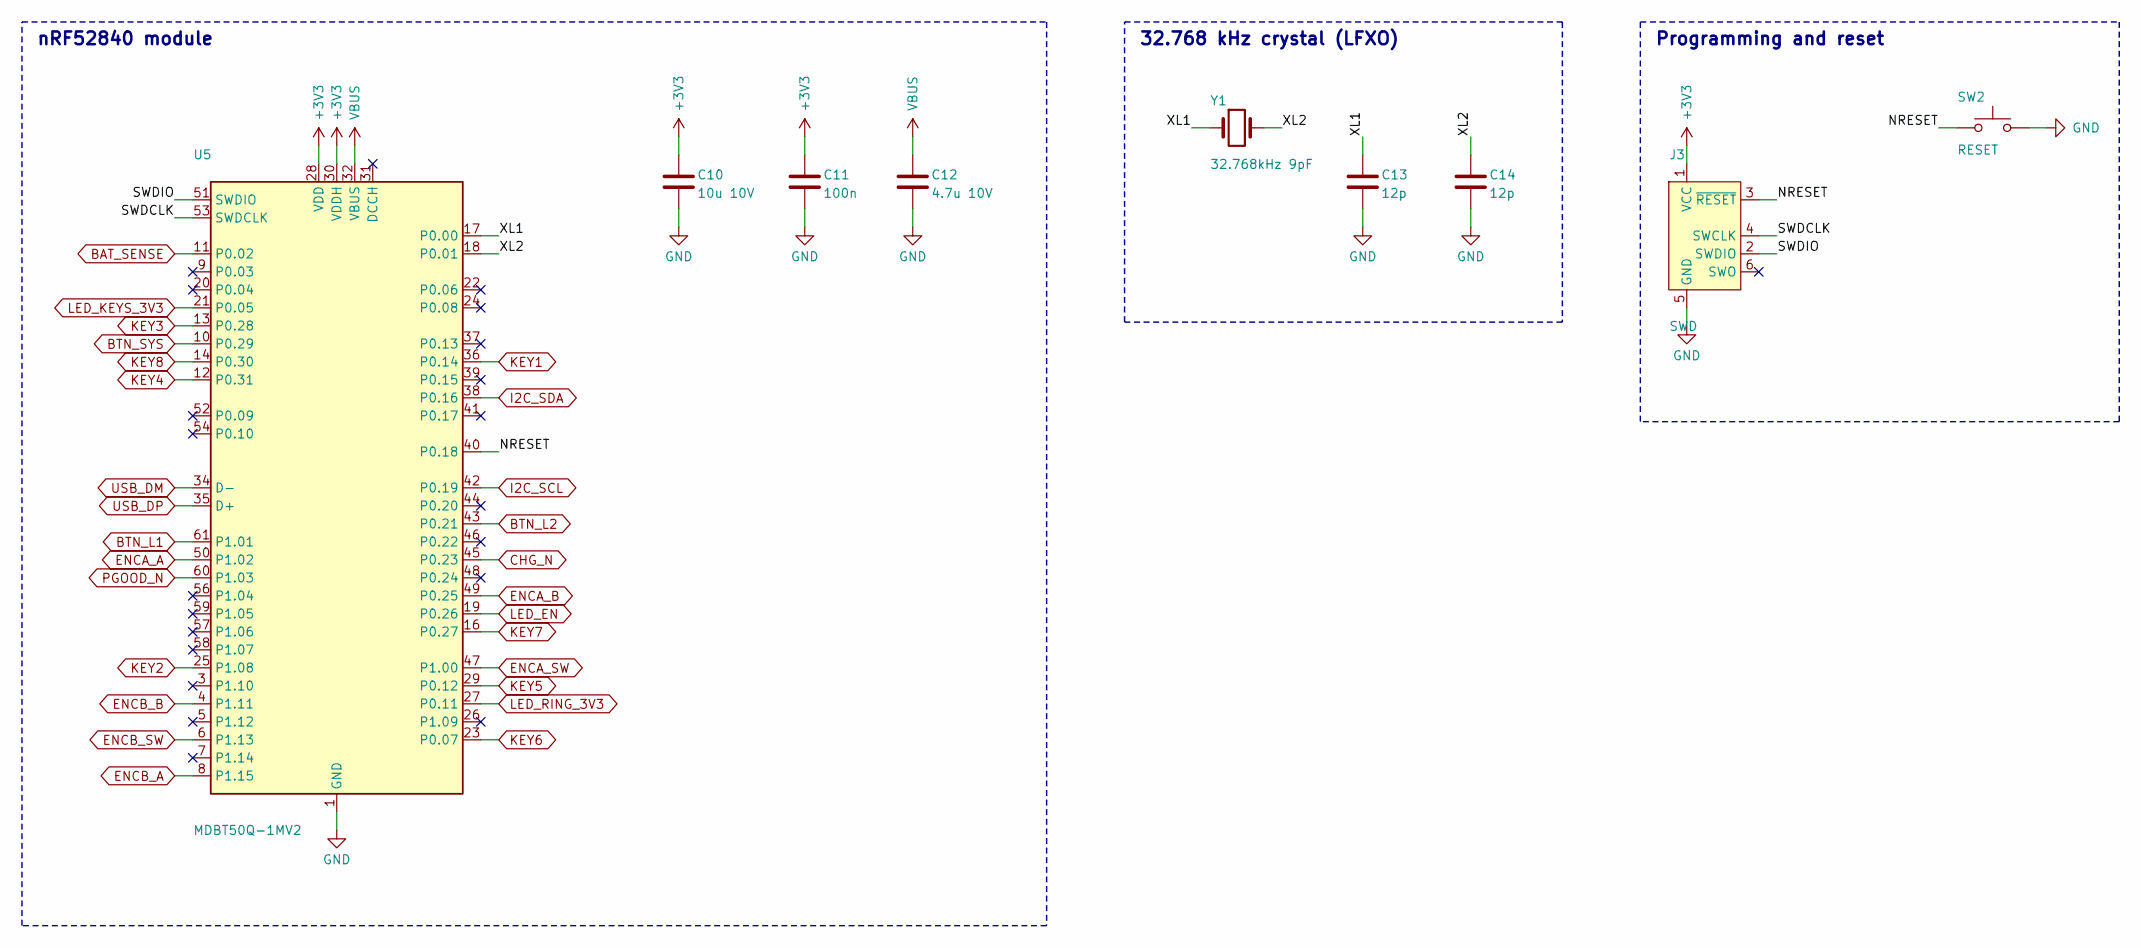
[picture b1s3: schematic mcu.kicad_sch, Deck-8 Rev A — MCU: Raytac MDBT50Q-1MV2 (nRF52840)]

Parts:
C10: 10u 10V; C_0603_1608Metric; MPN CL10A106KP8NNNC (10 V X5R); LCSC C19702
C11: 100n; C_0603_1608Metric; MPN CC0603KRX7R9BB104 (50 V X7R); LCSC C14663
C12: 4.7u 10V; C_0603_1608Metric; MPN CL10A475KO8NNNC (16 V X5R); LCSC C19666
C13, C14: 12p; C_0603_1608Metric; MPN CL10C120JB8NNNC (50 V C0G); LCSC C38523
J3: SWD; Tag-Connect_TC2030-IDC-NL_2x03_P1.27mm_Vertical
SW2: RESET; SW_SPST_PTS810; MPN C&K PTS810SJK250SMTRLFS; LCSC C221896
U5: MDBT50Q-1MV2; Raytac_MDBT50Q; MPN Raytac MDBT50Q-1MV2; LCSC C5118826
Y1: 32.768kHz 9pF; Crystal_SMD_3215-2Pin_3.2x1.5mm; MPN Seiko SC-32S 32.768kHz 20ppm 9pF; LCSC C97605

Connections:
+3V3: C10.1, C11.1, J3.1 (VCC), U5.28 (VDD), U5.30 (VDDH); also elsewhere on the board
/MCU/NRESET: J3.3 (~RESET), SW2.1, U5.40 (P0.18)
/MCU/SWDCLK: J3.4 (SWCLK), U5.53 (SWDCLK)
/MCU/SWDIO: J3.2 (SWDIO), U5.51 (SWDIO)
/MCU/XL1: C13.1, U5.17 (P0.00), Y1.1
/MCU/XL2: C14.1, U5.18 (P0.01), Y1.2
BAT_SENSE: U5.11 (P0.02); also elsewhere on the board
BTN_L1: U5.61 (P1.01); also elsewhere on the board
BTN_L2: U5.43 (P0.21); also elsewhere on the board
BTN_SYS: U5.10 (P0.29); also elsewhere on the board
CHG_N: U5.45 (P0.23); also elsewhere on the board
ENCA_A: U5.50 (P1.02); also elsewhere on the board
ENCA_B: U5.49 (P0.25); also elsewhere on the board
ENCA_SW: U5.47 (P1.00); also elsewhere on the board
ENCB_A: U5.8 (P1.15); also elsewhere on the board
ENCB_B: U5.4 (P1.11); also elsewhere on the board
ENCB_SW: U5.6 (P1.13); also elsewhere on the board
GND: C10.2, C11.2, C12.2, C13.2, C14.2, J3.5 (GND), SW2.2, U5.1 (GND), U5.2 (GND), U5.15 (GND), U5.33 (GND), U5.55 (GND); also elsewhere on the board
I2C_SCL: U5.42 (P0.19); also elsewhere on the board
I2C_SDA: U5.38 (P0.16); also elsewhere on the board
KEY1: U5.36 (P0.14); also elsewhere on the board
KEY2: U5.25 (P1.08); also elsewhere on the board
KEY3: U5.13 (P0.28); also elsewhere on the board
KEY4: U5.12 (P0.31); also elsewhere on the board
KEY5: U5.29 (P0.12); also elsewhere on the board
KEY6: U5.23 (P0.07); also elsewhere on the board
KEY7: U5.16 (P0.27); also elsewhere on the board
KEY8: U5.14 (P0.30); also elsewhere on the board
LED_EN: U5.19 (P0.26); also elsewhere on the board
LED_KEYS_3V3: U5.21 (P0.05); also elsewhere on the board
LED_RING_3V3: U5.27 (P0.11); also elsewhere on the board
PGOOD_N: U5.60 (P1.03); also elsewhere on the board
USB_DM: U5.34 (D-); also elsewhere on the board
USB_DP: U5.35 (D+); also elsewhere on the board
VBUS: C12.1, U5.32 (VBUS); also elsewhere on the board

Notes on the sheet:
nRF52840 module
32.768 kHz crystal (LFXO)
Programming and reset

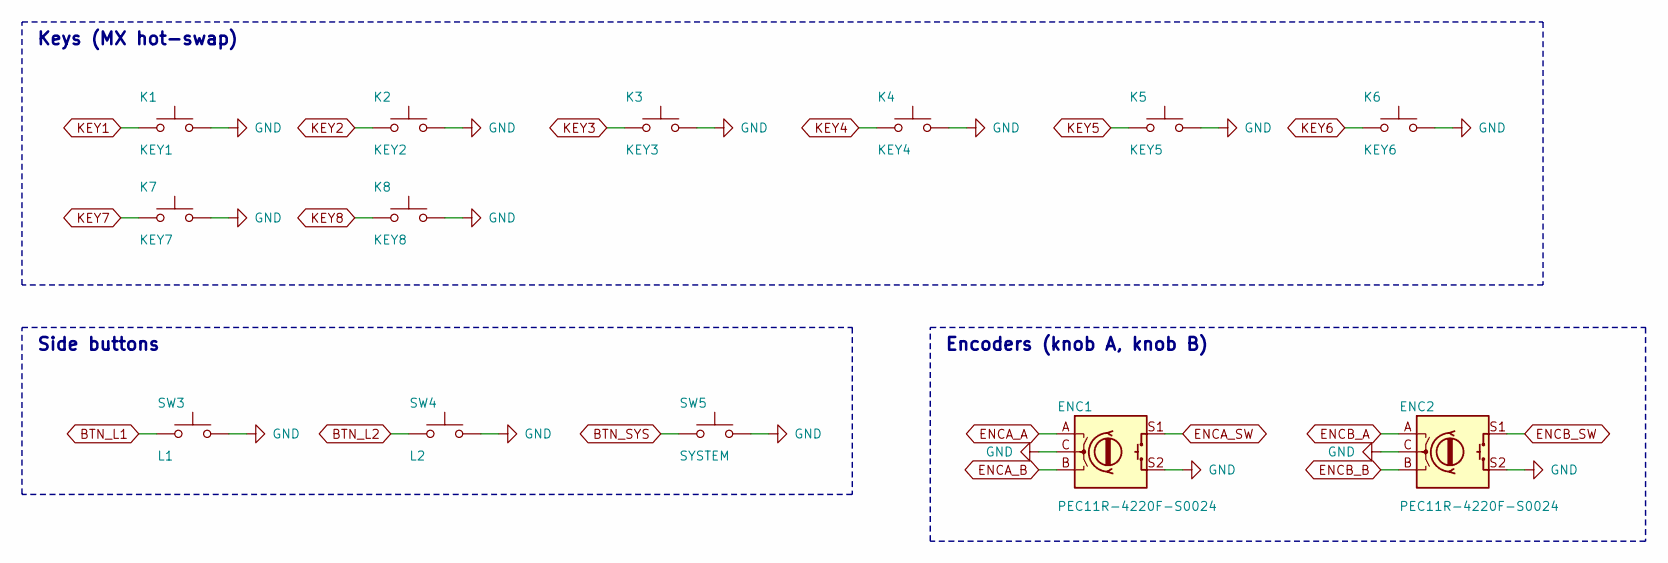
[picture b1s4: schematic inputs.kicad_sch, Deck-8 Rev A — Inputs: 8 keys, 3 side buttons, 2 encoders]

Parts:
ENC1, ENC2: PEC11R-4220F-S0024; RotaryEncoder_Alps_EC11E-Switch_Vertical_H20mm; MPN Bourns PEC11R-4220F-S0024
K1: KEY1; SW_MX_Hotswap_Kailh_1u_NorthLED; MPN HanElectricity CPG151101S11-16 (MX hot-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; LCSC C41430893
K2: KEY2; SW_MX_Hotswap_Kailh_1u_NorthLED; MPN HanElectricity CPG151101S11-16 (MX hot-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; LCSC C41430893
K3: KEY3; SW_MX_Hotswap_Kailh_1u_NorthLED; MPN HanElectricity CPG151101S11-16 (MX hot-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; LCSC C41430893
K4: KEY4; SW_MX_Hotswap_Kailh_1u_NorthLED; MPN HanElectricity CPG151101S11-16 (MX hot-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; LCSC C41430893
K5: KEY5; SW_MX_Hotswap_Kailh_1u_NorthLED; MPN HanElectricity CPG151101S11-16 (MX hot-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; LCSC C41430893
K6: KEY6; SW_MX_Hotswap_Kailh_1u_NorthLED; MPN HanElectricity CPG151101S11-16 (MX hot-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; LCSC C41430893
K7: KEY7; SW_MX_Hotswap_Kailh_1u_NorthLED; MPN HanElectricity CPG151101S11-16 (MX hot-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; LCSC C41430893
K8: KEY8; SW_MX_Hotswap_Kailh_1u_NorthLED; MPN HanElectricity CPG151101S11-16 (MX hot-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; LCSC C41430893
SW3: L1; SW_Push_1P1T-MP_NO_Horizontal_Alps_SKRTLAE010; MPN Alps SKRTLAE010; LCSC C110293
SW4: L2; SW_Push_1P1T-MP_NO_Horizontal_Alps_SKRTLAE010; MPN Alps SKRTLAE010; LCSC C110293
SW5: SYSTEM; SW_Push_1P1T-MP_NO_Horizontal_Alps_SKRTLAE010; MPN Alps SKRTLAE010; LCSC C110293

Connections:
BTN_L1: SW3.1; also elsewhere on the board
BTN_L2: SW4.1; also elsewhere on the board
BTN_SYS: SW5.1; also elsewhere on the board
ENCA_A: ENC1.A; also elsewhere on the board
ENCA_B: ENC1.B; also elsewhere on the board
ENCA_SW: ENC1.S1; also elsewhere on the board
ENCB_A: ENC2.A; also elsewhere on the board
ENCB_B: ENC2.B; also elsewhere on the board
ENCB_SW: ENC2.S1; also elsewhere on the board
GND: ENC1.C, ENC1.S2, ENC2.C, ENC2.S2, K1.2, K2.2, K3.2, K4.2, K5.2, K6.2, K7.2, K8.2, SW3.2, SW4.2, SW5.2; also elsewhere on the board
KEY1: K1.1; also elsewhere on the board
KEY2: K2.1; also elsewhere on the board
KEY3: K3.1; also elsewhere on the board
KEY4: K4.1; also elsewhere on the board
KEY5: K5.1; also elsewhere on the board
KEY6: K6.1; also elsewhere on the board
KEY7: K7.1; also elsewhere on the board
KEY8: K8.1; also elsewhere on the board

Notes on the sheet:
Keys (MX hot-swap)
Side buttons
Encoders (knob A, knob B)
